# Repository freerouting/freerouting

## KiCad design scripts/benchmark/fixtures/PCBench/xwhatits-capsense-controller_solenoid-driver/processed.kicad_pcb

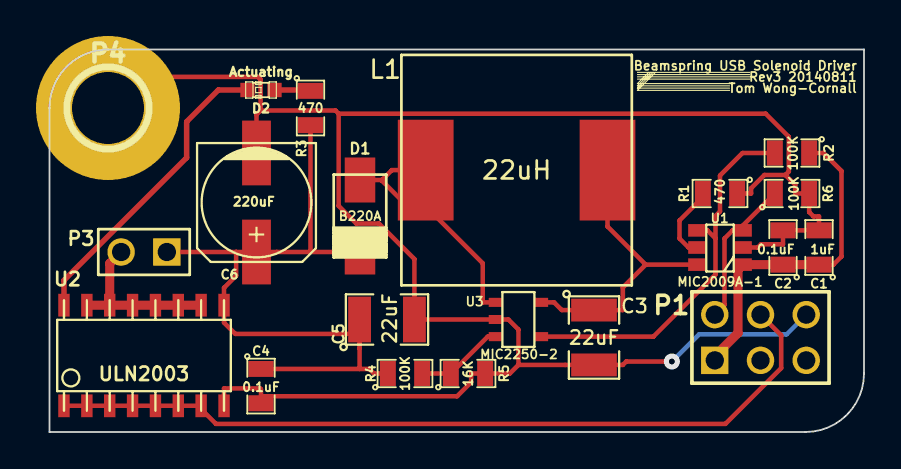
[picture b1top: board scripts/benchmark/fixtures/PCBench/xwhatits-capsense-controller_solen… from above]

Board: 2 copper layers, 45.2 x 21.2 mm, 21 parts (0 on the bottom side), 13 nets.

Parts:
C1: 1uF; SM0805
C2, C4: 0.1uF; SM0805
C3, C5: 22uF; SM1210
C6: 220uF; c_elec_6.3x7.7
D1: B220A; DO214AC_SMA
D2: Actuating; LED-0603
L1: 22uH; INDUCTOR_12.8x12.8
P1: CONN_3X2; pin_array_3x2
P3: CONN_2; PIN_ARRAY_2X1
P4: Chassis GND; 1pin
R1, R3: 470; SM0805
R2, R4, R6: 100K; SM0805
R5: 16K; SM0805
U1: MIC2009A-1; SOT23_6
U2: ULN2003; so-16
U3: MIC2250-2; SOT23-5

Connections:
+5V: C1.1, C2.1, P1.1, R2.1, U1.1
+9V: C4.1, C5.1, C6.1, D1.2, P3.1, R3.2, R4.1, U2.9
/+5V_Gated: C3.1, L1.1, U1.6, U3.5
/SW: D1.1, L1.2, U3.1
GND: C1.2, C2.2, C3.2, C4.2, C5.2, C6.2, P1.6, P4.1, R1.1, R5.2, R6.2, U1.2, U2.8, U3.2
unnamed: R1.2, U1.5
unnamed: P1.4, U2.1, U2.2, U2.3, U2.4, U2.5, U2.6, U2.7
unnamed: P3.2, U2.10, U2.11, U2.12, U2.13, U2.14, U2.15
unnamed: P1.2, R6.1, U1.3
unnamed: D2.2, U2.16
unnamed: D2.1, R3.1
unnamed: R2.2, U1.4, U3.4
unnamed: R4.2, R5.1, U3.3

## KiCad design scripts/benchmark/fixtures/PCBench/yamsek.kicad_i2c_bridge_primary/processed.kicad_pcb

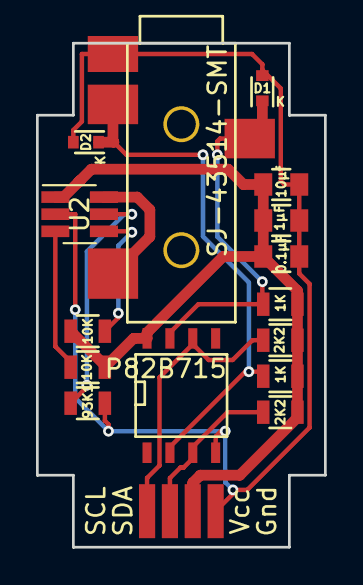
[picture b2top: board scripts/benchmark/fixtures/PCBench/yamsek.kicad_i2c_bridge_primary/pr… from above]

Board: 2 copper layers, 16.0 x 28.0 mm, 16 parts (0 on the bottom side), 10 nets.

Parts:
C1: 10µf; C_0805
C2: 1µF; C_0805
C3: 0.1µF; C_0805
D1, D2: VESD05a1; SOD-523
I2C1: CONN_01X04; solderPads_4_Grove_I2C
R1, R2: 1K; R_0805
R3, R4: 2K2; R_0805
R5, R6: 10K; R_0805
R7: 93K1; R_0805
TRRS1: SJ-43514-SMT; audio_smd_SJ-43514-SMT
U1: P82B715; SOIC-8-N
U2: AP2553W6; SOT-23-6_Handsoldering

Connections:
+5V: C1.1, C2.1, C3.1, I2C1.3, R1.2, R2.2, R3.2, R4.2, R5.1, R6.1, U1.8, U2.1
/i2c_bridge_common/SCL_connector: D1.1, R1.1, TRRS1.3, U1.7
/i2c_bridge_common/SCL_inside: I2C1.1, R3.1, U1.6
/i2c_bridge_common/SDA_connector: D2.1, R2.1, TRRS1.4, U1.2
/i2c_bridge_common/SDA_inside: I2C1.2, R4.1, U1.3
GND: C1.2, C2.2, C3.2, D1.2, D2.2, I2C1.4, R7.2, TRRS1.1, U1.4, U2.2
unnamed: R5.2, U2.4
unnamed: R6.2, U2.3
unnamed: R7.1, U2.5
unnamed: TRRS1.2, U2.6
